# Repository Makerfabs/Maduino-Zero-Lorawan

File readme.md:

# Maduino Zero Lorawan

```c++
/*
Version:		V1.3
Author:			Vincent
Create Date:	2021/5/19
Note:
		V2.0:Change for Ra08
		V1.3:Change Wiki Link
		V1.2:Add Maduino Zero Lorawan Change Frequence.docx
		V1.1:Add At command explain.
*/
```

[toc]

# Makerfabs

[Makerfabs home page](https://www.makerfabs.com/)

[Makerfabs Wiki](https://wiki.makerfabs.com/)

# Maduino Zero Lorawan
## Intruduce

Product Link ：[Maduino Zero LoRaWAN](https://www.makerfabs.com/maduino-zero-lorawan.html) 

Wiki Link :  [Maduino Zero LoRaWAN Node](http://wiki.makerfabs.com/Maduino_Zero_LoRaWAN_Node.html) 

Maduino Zero LoRaWan is a solution based on ATSAMD21G18 MCU and LoRaWAN module Ra-08H. The LoRaWAN module Ra-08H is based on the ASR6501 chip, it integrated the LoRa radio transceiver, LoRa modem, and 32-bit RISC MCU, to support LoRa modulation mode and (G) FSK modulation mode. Maduino LoRaWan acts as a LoRaWAN node to transmit/receive the local data to the network by connecting LoRaWAN Gateway. With this module, users are easy to prototype LoRaWAN projects easily in few hours.

## Feature

- ATSAMD21G18, 32-Bit ARM Cortex M0+
- Interface: I2C/SPI/UART/18*GPIO
- With super anti-interference ability, it can work normally in complex interference environment.
- Minimum receiving sensitivity: -137dBm (SF=12/BW=125KHz)
- Maximum transmit power +21dBm
- Working frequency: (Ra-07) 410mhz ~ 525mhz (default), (Ra-07h) 803mhz ~ 930mhz (default)
- Power supply voltage input: 3.3V
- Transmitting working current: 107mA (full load power consumption)
- Receive working current: 6mA
- Sleep current: 3uA

### Front:

### Back:

# Example

## V2.0 Change Frequence

The module supports 868MHz and 915MHz Lorawan communication, but requires upload different firmware.

**You must need  Makerfabs Down tools or USB to TTL tools**

[MakerFabs CP2104 USB2UART](https://www.makerfabs.com/cp2104-usb-to-serial-converter.html)

1, Open firmware_update_tool/ TremoProgrammer_v0.8.exe

2, Select firmware you need.

3, Connect MakerFabs CP2104 USB2UART to Maduino Zero Lorawan.

| USB2UART | Maduino Zero Lorawan |
| -------- | -------------------- |
| VCC      | 3.3V                 |
| GND      | GND                  |
| TX       | CLK                  |
| RX       | DIO                  |

4, Connect J10 and 3V3 with a wire

5, Click Download

6, Press RESET button on Maduino

7, Wait download over

## Compiler Options
**If you have any questions，such as how to install the development board, how to download the code, how to install the library. Please refer to :[Makerfabs_FAQ](https://github.com/Makerfabs/Makerfabs_FAQ)**

- Install library : DHT_sensor_library.
- Upload codes, select "Arduino Zero" and "Native USB"

## Example List

### at-test

Simple at command test demo

### at-test-lorawan

Register the Lorawan gateway in OTA mode and send data to the TTN. And send message to ThingSpeak.

### test_SD

Simple SD card test for read and write.

### downlink_control

Using TTN console send a download message to Maduino. 

## AT Command Explain

### AT+CDEVEUI?

*Inquire DEVEUI right now.*

AT+CDEVEUI?

### AT+CDEVEUI=&lt;DevEUI&gt;

*Set DEVEUI, APPEUI and APPKEY.*

AT+CDEVEUI=&lt;DevEUI:length is 16&gt;
AT+CAPPEUI=&lt;AppEUI:length is 16&gt;
AT+CAPPKEY=&lt;AppKey:length is 32&gt;

OTAA join mode need these three numbers.

### AT+CJOINMODE=&lt;MODE&gt;

*Set join mode via OTAA.*

AT+CJOINMODE=&lt;MODE&gt;
&lt;MODE&gt;
0：OTAA
1：ABP
Defualt mode is OTAA.

AT+CJOINMODE=0

### AT+CCLASS=&lt;MODE&gt;

*Set lorwan mode.*

AT+CJOINMODE=&lt;MODE&gt;
&lt;MODE&gt;
0：ClassA
1：ClassB
2：ClassC

Defualt mode is ClassA.

AT+CCLASS=0

### AT+CJOIN=&lt;ParaValue1&gt;,[ParaValue2],…[ParaValue4]

*Join Lorawan to Lorawan webgate.*

AT+CJOIN=&lt;ParaValue1&gt;,[ParaValue2],…[ParaValue4]

&lt;ParaTag1&gt;

0: Stop JOIN
1: Start JOIN

[ParaValue2]

0: Disable Auto JOIN
1: Enable Auto JOIN

[ParaValue3]

JOIN cycle,range 7 to 255, unit is second。
Default value is 8.

[ParaValue4]

Maximum number of access attempts,range 1 to 256.

AT+CJOIN=1,0,10,1
Set JOIN parameter: Start join, disable automatic join, try period is 10s, maximum attempt times is 8.

### AT+DTRX=[confirm],[nbtrials],&lt;Length&gt;,&lt;Payload&gt;

*Send one message to webgate,and receive message.*

AT+DTRX=[confirm],[nbtrials],&lt;Length&gt;,&lt;Payload&gt;

[confirm]

0: UnConfirmed up message

1: Confirmed up message

[nbtrials]

Set sending times.
Confirm and nbtrials refer to the corresponding AT instruction, valid for this dispatch only, optional.

&lt;Length&gt;

Represents the number of strings. The maximum value is specified in the access specification. 
The length of bytes allowed to be transmitted is different at different rates (see the Lorawan protocol for details). 
0 indicates that empty packets are sent.

&lt;Payload&gt;

Hexadecimal (2 characters for 1 number)

AT+DTRX=1,2,5,0123456789

OK+SEND:05

OK+SENT:01

OK+RECV:02,01,00

Confirm data sent successfully, valid data received by server should be 0x01 0x23 0x45 0x67 0x89.
And received downlink confirmation 0x02,0x01,0x00.

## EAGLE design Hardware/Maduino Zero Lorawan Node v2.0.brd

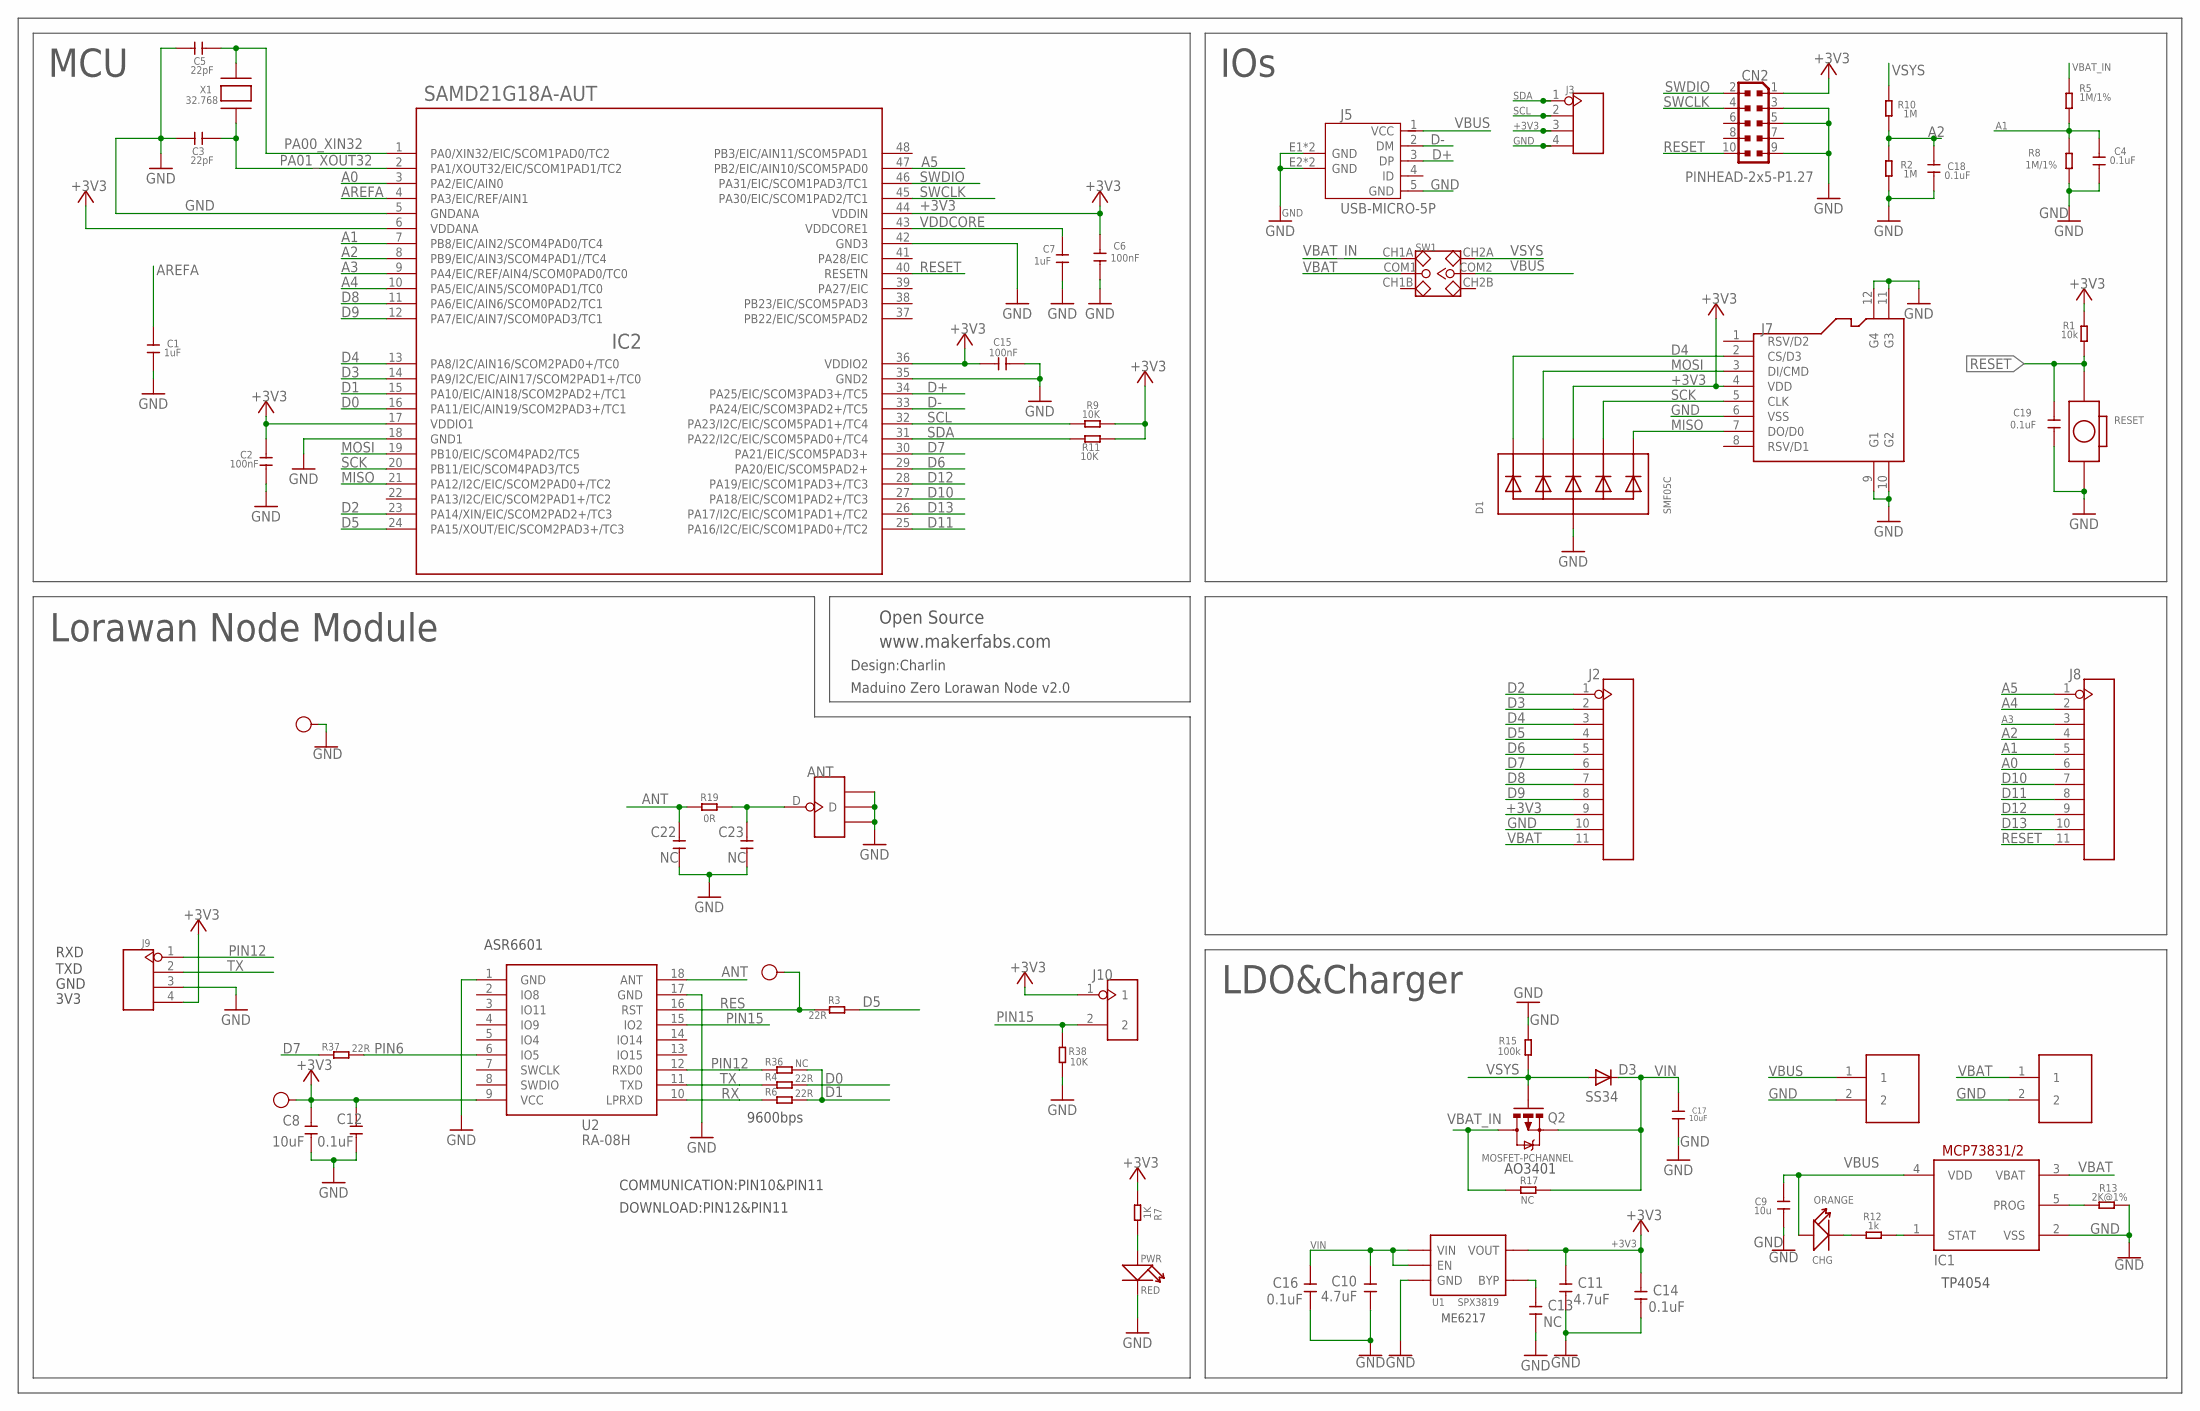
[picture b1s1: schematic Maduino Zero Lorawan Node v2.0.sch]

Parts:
3V3: TEST-POINT'4545'; TP-D45MIL; PARTNO DNP
ANT: ANTENNA-U-FL; 4P-U-FL
C1, C7: 1uF; 0603
C2, C6, C15: 100nF; 0603
C3, C5: 22pF; 0603
C4, C12, C14, C16, C18, C19: 0.1uF; 0603
C8, C17: 10uF; 0603
C9: 10u; 0603
C10, C11: 4.7uF; 0603
C13, C22, C23: NC; 0603
CHG: ORANGE; D0603
CN2: PINHEAD-2x5-P1.27; PINHEAD_2X05_127
D1: SMF05C; SOT363
D3: SS34; DO-214AC
GND: TEST-POINT'4545'; TP-D45MIL
IC1: MCP73831/OT; SOT23-5L
IC2: SAMD21G18A-AUT; TQFP48-7X7
J1, J6: PH2.0-2P-90-DIP
J2, J8: HEADER-11P-2.54; 11P-2.54
J3, J9: HEADER-4P-60/35MILROUND; 4P-65/35ROUND
J5: USB-MICRO-5P; MICRO-USB-5P
J7: HOLDER-MICROSD-8P; 8P-SMD
J10: HEADER-2P-2.0; 2P-2.0
PWR: RED; LED-0603
Q2: MOSFET-PCHANNEL; SOT23-3
R1: 10k; R0603
R2, R10: 1M; R0603
R3, R4, R6, R37: 22R; R0603
R5, R8: 1M/1%; R0603
R7: 1K; R0603
R9, R11, R38: 10K; R0603
R12: 1k; R0603
R13: 2K@1%; R0603
R15: 100k; R0603
R17, R36: NC; R0603
R19: 0R; R0603
RESET: BOTTON-2P-90D; 2P-7.62X3.56-90D
RST: TEST-POINT'4545'; TP-D45MIL; PARTNO DNP
SW1: SWITCH-2CH-6P; 6P-2CH-2.54-7.6X3.0
U1: SPX3819; SOT23-5
U2: RA-08H
X1: 32.768; XTAL3215

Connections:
+3V3: 3V3.T, C2.2, C6.1, C8.2, C11.2, C12.2, C14.2, C15.1, CN2.1, D1.4 (C3), IC2.6 (VDDANA), IC2.17 (VDDIO1), IC2.36 (VDDIO2), IC2.44 (VDDIN), J2.9, J3.3, J7.4 (VDD), J9.4, J10.1, R1.2, R7.1, R9.2, R11.2, U1.5 (VOUT), U2.9 (VCC)
A0: IC2.3 (PA2/EIC/AIN0), J8.6
A1: C4.1, IC2.7 (PB8/EIC/AIN2/SCOM4PAD0/TC4), J8.5, R5.1, R8.2
A2: C18.1, IC2.8 (PB9/EIC/AIN3/SCOM4PAD1//TC4), J8.4, R2.2, R10.1
A3: IC2.9 (PA4/EIC/REF/AIN4/SCOM0PAD0/TC0), J8.3
A4: IC2.10 (PA5/EIC/AIN5/SCOM0PAD1/TC0), J8.2
A5: IC2.47 (PB2/EIC/AIN10/SCOM5PAD0), J8.1
ANT: C22.2, R19.1, U2.18 (ANT)
AREFA: C1.1, IC2.4 (PA3/EIC/REF/AIN1)
D0: IC2.16 (PA11/EIC/AIN19/SCOM2PAD3+/TC1), R4.2
D1: IC2.15 (PA10/EIC/AIN18/SCOM2PAD2+/TC1), R6.2, R36.2
D2: IC2.23 (PA14/XIN/EIC/SCOM2PAD2+/TC3), J2.1
D3: IC2.14 (PA9/I2C/EIC/AIN17/SCOM2PAD1+/TC0), J2.2
D4: D1.1 (C1), IC2.13 (PA8/I2C/AIN16/SCOM2PAD0+/TC0), J2.3, J7.2 (CS/D3)
D5: IC2.24 (PA15/XOUT/EIC/SCOM2PAD3+/TC3), J2.4, R3.2
D6: IC2.29 (PA20/EIC/SCOM5PAD2+), J2.5
D7: IC2.30 (PA21/EIC/SCOM5PAD3+), J2.6, R37.1
D8: IC2.11 (PA6/EIC/AIN6/SCOM0PAD2/TC1), J2.7
D9: IC2.12 (PA7/EIC/AIN7/SCOM0PAD3/TC1), J2.8
D10: IC2.27 (PA18/EIC/SCOM1PAD2+/TC3), J8.7
D11: IC2.25 (PA16/I2C/EIC/SCOM1PAD0+/TC2), J8.8
D12: IC2.28 (PA19/EIC/SCOM1PAD3+/TC3), J8.9
D13: IC2.26 (PA17/I2C/EIC/SCOM1PAD1+/TC2), J8.10
D+: IC2.34 (PA25/EIC/SCOM3PAD3+/TC5), J5.3 (DP)
D-: IC2.33 (PA24/EIC/SCOM3PAD2+/TC5), J5.2 (DM)
GND: ANT.GND1, ANT.GND2, ANT.GND3, C1.2, C2.1, C3.2, C4.2, C5.2, C6.2, C7.2, C8.1, C9.1, C10.1, C11.1, C12.1, C13.1, C14.1, C15.2, C16.1, C17.1, C18.2, C19.1, C22.1, C23.1, CN2.3, CN2.5, CN2.9, D1.2 (A), GND.T, IC1.2 (VSS), IC2.5 (GNDANA), IC2.18 (GND1), IC2.35 (GND2), IC2.42 (GND3), J1.2, J2.10, J3.4, J5.5 (GND), J5.E1 (GND), J5.E2 (GND), J5.P1 (GND), J5.P2 (GND), J6.2, J7.6 (VSS), J7.9 (G1), J7.10 (G2), J7.11 (G3), J7.12 (G4), J9.3, PWR.-, R2.1, R8.1, R13.2, R15.2, R38.2, RESET.P$2 (2), U1.2 (GND), U2.1 (GND), U2.17 (GND)
MISO: D1.6 (C5), IC2.21 (PA12/I2C/EIC/SCOM2PAD0+/TC2), J7.7 (DO/D0)
MOSI: D1.3 (C2), IC2.19 (PB10/EIC/SCOM4PAD2/TC5), J7.3 (DI/CMD)
unnamed: PWR.+, R7.2
unnamed: ANT.D, C23.2, R19.2
unnamed: CHG.-, R12.1
unnamed: IC1.1 (STAT), R12.2
unnamed: IC1.5 (PROG), R13.1
unnamed: C13.2, U1.4 (BYP)
PA00_XIN32: C5.1, IC2.1 (PA0/XIN32/EIC/SCOM1PAD0/TC2), X1.P$2
PA01_XOUT32: C3.1, IC2.2 (PA1/XOUT32/EIC/SCOM1PAD1/TC2), X1.P$1
PIN6: R37.2, U2.6 (IO5)
PIN12: J9.1, R36.1, U2.12 (RXD0)
PIN15: J10.2, R38.1, U2.15 (IO2)
RES: R3.1, RST.T, U2.16 (RST)
RESET: C19.2, CN2.10, IC2.40 (RESETN), J8.11, R1.1, RESET.P$1 (1)
RX: R6.1, U2.10 (LPRXD)
SCK: D1.5 (C4), IC2.20 (PB11/EIC/SCOM4PAD3/TC5), J7.5 (CLK)
SCL: IC2.32 (PA23/I2C/EIC/SCOM5PAD1+/TC4), J3.2, R9.1
SDA: IC2.31 (PA22/I2C/EIC/SCOM5PAD0+/TC4), J3.1, R11.1
SWCLK: CN2.4, IC2.45 (PA30/EIC/SCOM1PAD2/TC1)
SWDIO: CN2.2, IC2.46 (PA31/EIC/SCOM1PAD3/TC1)
TX: J9.2, R4.1, U2.11 (TXD)
VBAT: IC1.3 (VBAT), J2.11, J6.1, SW1.COM1
VBAT_IN: Q2.3 (D), R5.2, R17.1, SW1.CH1A
VBUS: C9.2, CHG.+, IC1.4 (VDD), J1.1, J5.1 (VCC), SW1.COM2
VDDCORE: C7.1, IC2.43 (VDDCORE1)
VIN: C10.2, C16.2, C17.2, D3.C, Q2.2 (S), R17.2, U1.1 (VIN), U1.3 (EN)
VSYS: D3.A, Q2.1 (G), R10.2, R15.1, SW1.CH2A

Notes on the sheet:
Lorawan Node Module
www.makerfabs.com
MCU
IOs
LDO&Charger
Design:Charlin
Open Source
AO3401
Maduino Zero Lorawan Node v2.0
ASR6601
COMMUNICATION:PIN10&PIN11
DOWNLOAD:PIN12&PIN11
9600bps
RXD
TXD
GND
3V3
ME6217
TP4054

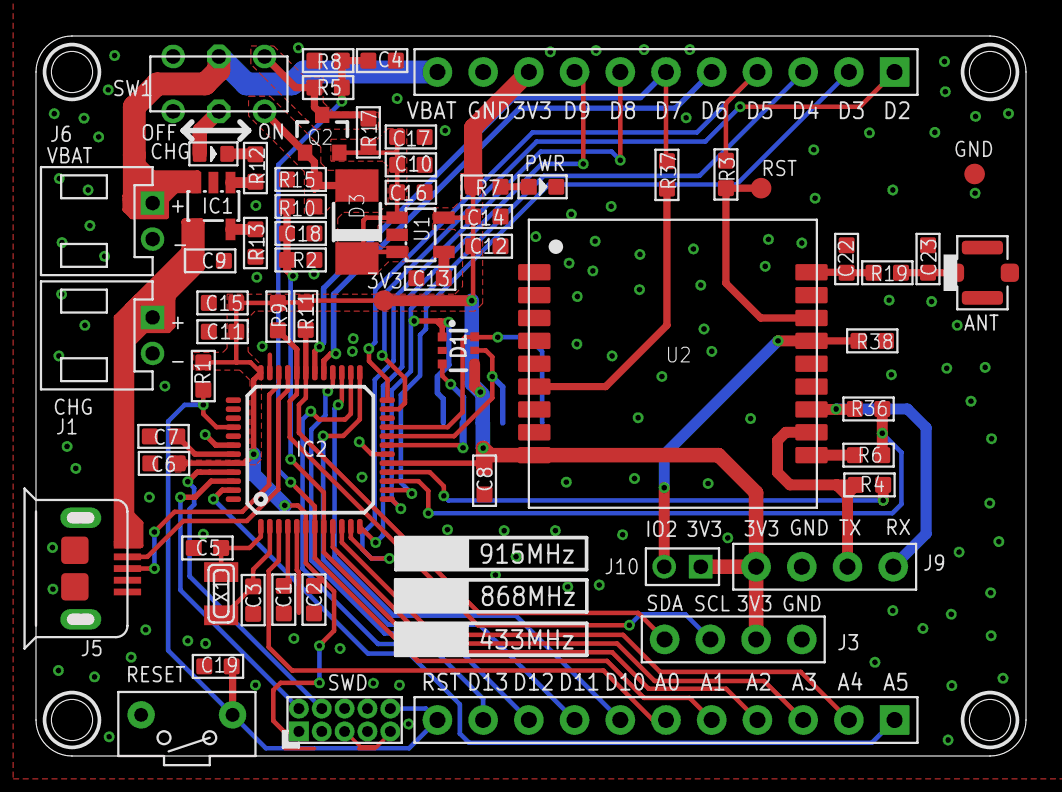
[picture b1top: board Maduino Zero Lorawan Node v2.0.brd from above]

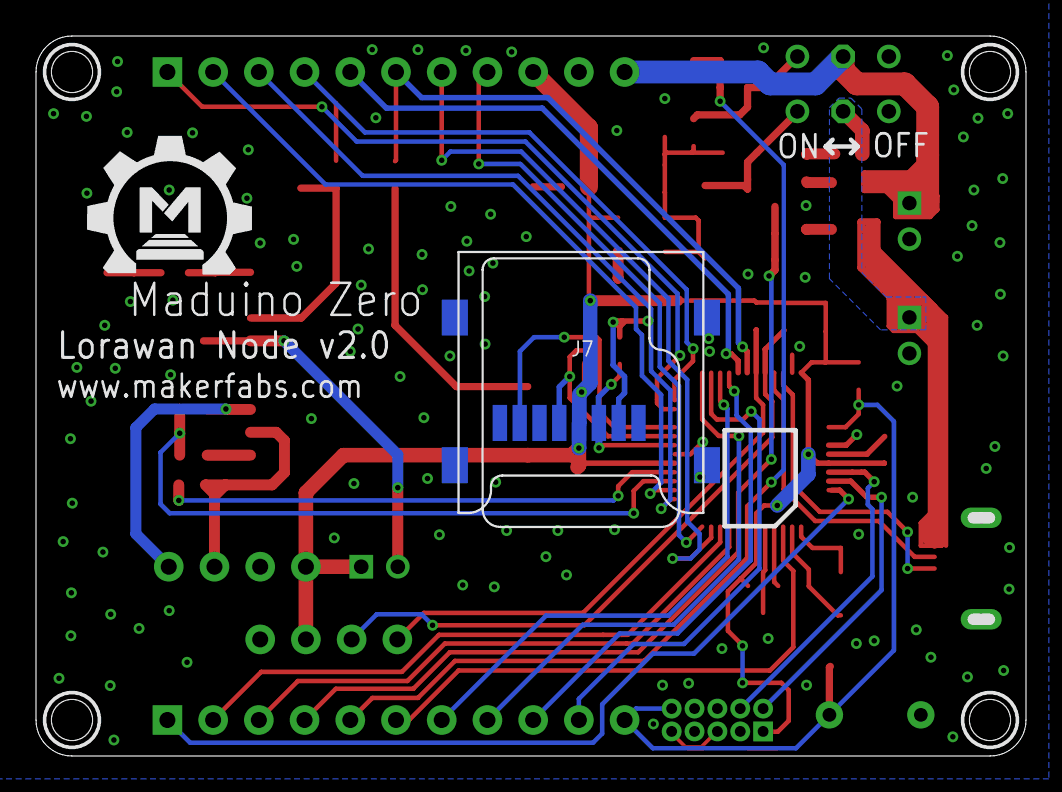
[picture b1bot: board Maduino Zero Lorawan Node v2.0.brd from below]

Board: 2 copper layers, 55.0 x 40.0 mm, 67 parts (2 on the bottom side), 54 nets.

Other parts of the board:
U$1: MAKERFABS_0.3

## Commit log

2021-05-19 Create Demo
2021-05-22 create hardware
2021-06-01 fix bug
2021-06-29 At at command explain.
2021-08-18 Create SD demo
2021-10-13 Add firmware
2022-12-06 Add downlink control example
2023-03-01 Hardware update
2023-03-02 Fix for RA08
2023-03-02 Edit readme

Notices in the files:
parts and their libraries:
microbuilder: This work is placed in the public domain, and may be freely used for commercial and non-commercial work with the following conditions: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
User-Submitted: Licensing: Creative Commons ShareAlike 4.0 International - https://creativecommons.org/licenses/by-sa/4.0
